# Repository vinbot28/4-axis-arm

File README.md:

# 4 Axis Arm
The **4 Axis Arm** is exactly what you think it is. Using 4 servos, the robotic arm achieves 4 degree of freedom movement through the: turret base, shoulder, elbow, and wrist rotation joints. All of the 3d printed parts are designed to use zero to no supports, and there are very few parts in the whole assembly. I've also created an electronics box containing potentiometers, an Arduino Nano (for its popularity and accessibility), and a custom PCB to greatly decrease the wiring hassle. 

\
The wiring diagram for the potentiometers to PCB.

I created this project after seeing so many 6 axis arms pop up all over YouTube. Wanting one of my own, I quickly realized how much the components costed and the complexity of the control systems. Despite that, I really wanted to design and play with a robotic arm, and hence the decision to make a 4 axis. Additionally, I couldn't pass down the opportunity to CAD and design a PCB...

# General Instructions:
## Wiring: 
The PCB Silkscreen includes labels for which ports correspond to what component. Px = potentiometer; Sx = servo.\
Potentiometers:
- Pot 1      -> P1 (pcb) = Pin 19 (arduino)
- Pot 2      -> P2 (pcb) = Pin 20 (arduino) 
- Pot 3      -> P3 (pcb) = Pin 21 (arduino)
- Pot 4      -> P4 (pcb) = Pin 22 (arduino)
- Pot 5/claw -> P5 (pcb) = Pin 23 (arduino)

Servos:
- Servo 1/turret   -> S1 (pcb) = Pin 6 (arduino)
- Servo 2/shoulder -> S2 (pcb) = Pin 8 (arduino)
- Servo 3/elbow    -> S3 (pcb) = Pin 9 (arduino)
- Servo 4/wrist    -> S4 (pcb) = Pin 12 (arduino)
- Servo 5/effector -> S5 (pcb) = Pin 14 (arduino)

## Programming:
A sample program is included in this repository to control the servos using the potentiometers. Feel free to create your own programs to run pre-programmed movements, serial-based control, and much more!

# Bill of Materials:

| Item name             | Amount Needed       | Packs to buy    | Total Cost | Link                                                 |
|-----------------------|---------------------|-----------------|------------|------------------------------------------------------|
| MG946R Servo          |                   4 |               4 |      14.52 | https://www.aliexpress.us/item/3256806315358281.html |
| M4 6x5 Heat set       |                  23 |               1 |       2.64 | https://www.aliexpress.us/item/3256803396040989.html |
| M3 3x5 Heat set       |                   3 |               1 |       2.05 | https://www.aliexpress.us/item/3256803396040989.html |
| M4-6 SHCS             |                  20 |               1 |       1.55 | https://www.aliexpress.us/item/2255800598515019.html |
| M4-8 SHCS             |                   3 |               1 |       1.64 | https://www.aliexpress.us/item/2255800598515019.html |
| M3-6 SHCS             |                   3 |               1 |       1.41 | https://www.aliexpress.us/item/2255800598515019.html |
| Male/Female headers   |                   1 |               1 |       2.21 | https://www.aliexpress.us/item/2255800687544049.html |
| Female DC barrel jack |                   1 |               1 |       1.53 | https://www.aliexpress.us/item/3256802343987191.html |
| Arduino nano          |                     |               1 |       5.73 | https://www.aliexpress.us/item/3256806718205824.html |
| PCB                   |                     |               1 |          5 | jlcpcb.com                                           |
|                       |                     |                 |            |                                                      |
| 5v AC-DC Power supply |                   1 |               1 |       9.99 | https://a.co/d/4vrQsQI                               |
|                       |                     |                 |            |                                                      |
|                       |                     | Subtotal:       |      48.27 |                                                      |
|                       |                     | Grand Total     |      58.31 |                                                      |
| JLC Shipping          | Aliexpress Shipping | Amazon Shipping |            |                                                      |
|                   3.2 |                6.84 | N/A             |            |                                                      |

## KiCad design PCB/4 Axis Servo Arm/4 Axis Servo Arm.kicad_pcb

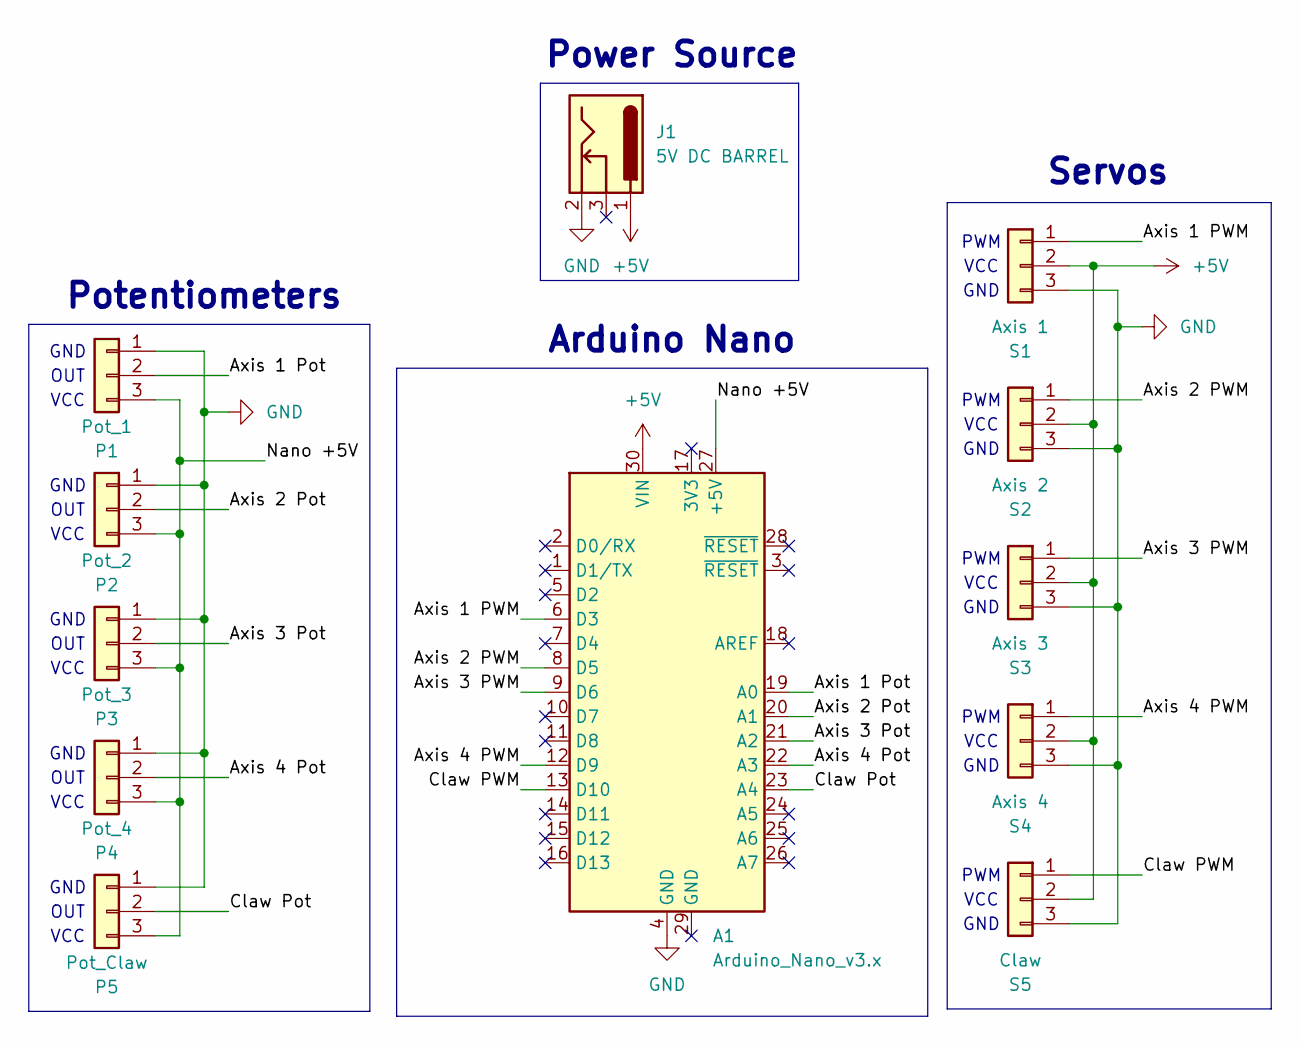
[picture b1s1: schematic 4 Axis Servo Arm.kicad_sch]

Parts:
A1: Arduino_Nano_v3.x; Arduino_Nano
J1: 5V DC BARREL; BarrelJack_Horizontal
P1: Pot_1; PinHeader_1x03_P2.54mm_Vertical
P2: Pot_2; PinHeader_1x03_P2.54mm_Vertical
P3: Pot_3; PinHeader_1x03_P2.54mm_Vertical
P4: Pot_4; PinHeader_1x03_P2.54mm_Vertical
P5: Pot_Claw; PinHeader_1x03_P2.54mm_Vertical
S1: Axis 1; PinHeader_1x03_P2.54mm_Vertical
S2: Axis 2; PinHeader_1x03_P2.54mm_Vertical
S3: Axis 3; PinHeader_1x03_P2.54mm_Vertical
S4: Axis 4; PinHeader_1x03_P2.54mm_Vertical
S5: Claw; PinHeader_1x03_P2.54mm_Vertical

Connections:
+5V: A1.30 (VIN), J1.1, S1.2, S2.2, S3.2, S4.2, S5.2
/Axis 1 PWM: A1.6 (D3), S1.1
/Axis 1 Pot: A1.19 (A0), P1.2
/Axis 2 PWM: A1.8 (D5), S2.1
/Axis 2 Pot: A1.20 (A1), P2.2
/Axis 3 PWM: A1.9 (D6), S3.1
/Axis 3 Pot: A1.21 (A2), P3.2
/Axis 4 PWM: A1.12 (D9), S4.1
/Axis 4 Pot: A1.22 (A3), P4.2
/Claw PWM: A1.13 (D10), S5.1
/Claw Pot: A1.23 (A4), P5.2
/Nano +5V: A1.27 (+5V), P1.3, P2.3, P3.3, P4.3, P5.3
GND: A1.4 (GND), J1.2, P1.1, P2.1, P3.1, P4.1, P5.1, S1.3, S2.3, S3.3, S4.3, S5.3

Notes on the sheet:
GND
PWM
VCC
GND
Servos
Potentiometers
Power Source
OUT
Arduino Nano

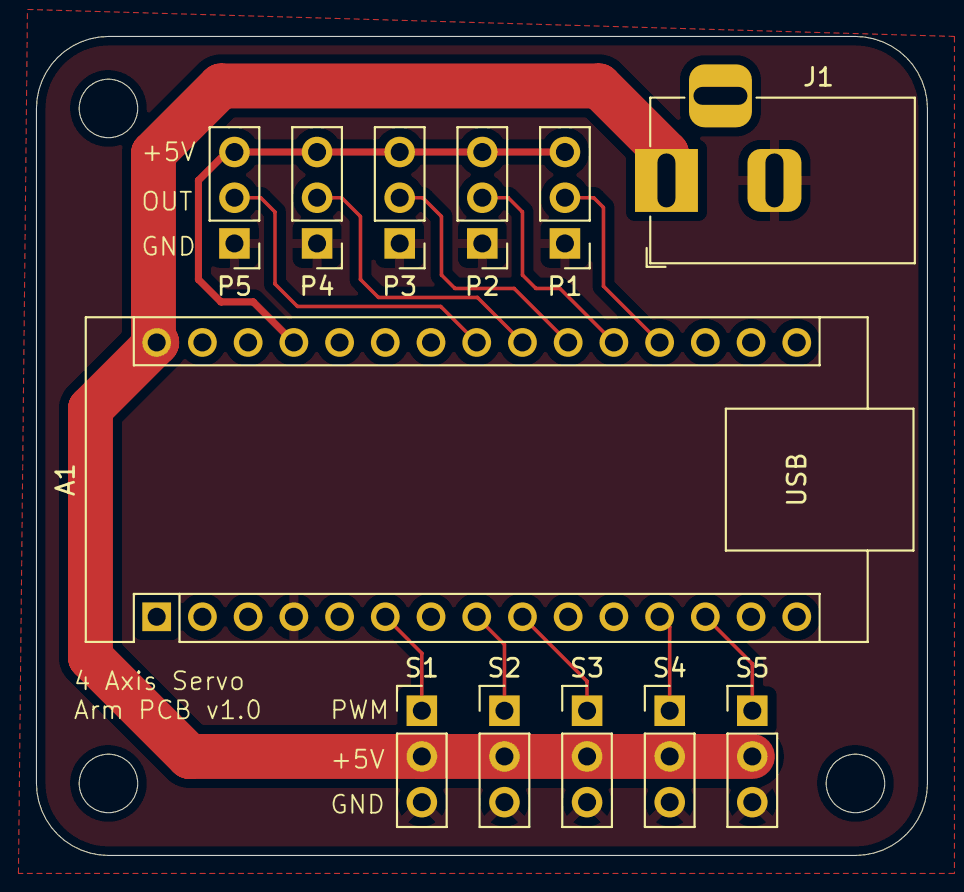
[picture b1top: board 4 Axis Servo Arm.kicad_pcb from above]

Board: 2 copper layers, 49.5 x 45.5 mm, 12 parts (0 on the bottom side), 13 nets.

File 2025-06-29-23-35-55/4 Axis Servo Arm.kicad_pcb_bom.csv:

Designator,Quantity,Value,Footprint,Package,MPN,DNP,Mount_Type,Description
A1,1,Arduino_Nano_v3.x,Arduino_Nano,,,,tht,Arduino Nano v3.x
J1,1,5V DC BARREL,BarrelJack_Horizontal,,,,tht,DC Barrel Jack with an internal switch
P1,1,Pot_1,PinHeader_1x03_P2.54mm_Vertical,,,,tht,"Generic connector, single row, 01x03, script generated (kicad-library-utils/schlib/autogen/connector/)"
P2,1,Pot_2,PinHeader_1x03_P2.54mm_Vertical,,,,tht,"Generic connector, single row, 01x03, script generated (kicad-library-utils/schlib/autogen/connector/)"
P3,1,Pot_3,PinHeader_1x03_P2.54mm_Vertical,,,,tht,"Generic connector, single row, 01x03, script generated (kicad-library-utils/schlib/autogen/connector/)"
P4,1,Pot_4,PinHeader_1x03_P2.54mm_Vertical,,,,tht,"Generic connector, single row, 01x03, script generated (kicad-library-utils/schlib/autogen/connector/)"
P5,1,Pot_Claw,PinHeader_1x03_P2.54mm_Vertical,,,,tht,"Generic connector, single row, 01x03, script generated (kicad-library-utils/schlib/autogen/connector/)"
S1,1,Axis 1,PinHeader_1x03_P2.54mm_Vertical,,,,tht,"Generic connector, single row, 01x03, script generated (kicad-library-utils/schlib/autogen/connector/)"
S2,1,Axis 2,PinHeader_1x03_P2.54mm_Vertical,,,,tht,"Generic connector, single row, 01x03, script generated (kicad-library-utils/schlib/autogen/connector/)"
S3,1,Axis 3,PinHeader_1x03_P2.54mm_Vertical,,,,tht,"Generic connector, single row, 01x03, script generated (kicad-library-utils/schlib/autogen/connector/)"
S4,1,Axis 4,PinHeader_1x03_P2.54mm_Vertical,,,,tht,"Generic connector, single row, 01x03, script generated (kicad-library-utils/schlib/autogen/connector/)"
S5,1,Claw,PinHeader_1x03_P2.54mm_Vertical,,,,tht,"Generic connector, single row, 01x03, script generated (kicad-library-utils/schlib/autogen/connector/)"

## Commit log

2025-06-30 added production files
2025-06-30 updating stuff
2025-06-30 kicad files
2025-06-30 added kicad files and renamed folders
